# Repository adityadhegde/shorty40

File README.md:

# The Shorty40
An ortholinear 39key keyboard with a 2U spacebar and KMK support using a Raspberry Pi Pico

## Bill of Materials

### Cost Saving Open Build
* Printed circuit board
* Raspberry Pi Pico or clones with same dimensions and GPIO Layouts with male headers attached 
* 39 1N4148 Diodes - through hole version
* 39 CherryMX Compatible plate mount switches
* 38 1U Keycaps and 1 2U Keycaps
* 1 2U plate mount stabilizer
* 1 3D Printed key plate
* 1 Laser Cut bottom plate
* 4 M2 Stand-Offs with  minimum 20mm clearance
* 8 5mm M2 screws
* 4 adhesive silicone/rubber foot - recommended but not required

### Close Case Build
* Printed circuit board
* Raspberry Pi Pico or clones with same dimensions and GPIO Layouts 
* 2 20 Pin male headers for the Pi Pico
* 2 20 Pin male to female headers for PCB
* 39 1N4148 Diodes - through hole version
* Hot Swap Sockets - tested with Millmax 0305 Socket
* 39 CherryMX Compatible plate mount switches
* 38 1U Keycaps and 1 2U Keycaps
* 1 2U plate mount stabilizer
* 1 3D Printed key plate
* 1 3D Printed Case - testing in process
* 8 5mm M2 screws
* 4 adhesive silicone/rubber foot

## Software Setup
1. Install [circuit python](https://circuitpython.org/)
2. Get [KMK](https://github.com/KMKfw/kmk_firmware/archive/refs/heads/master.zip) and unzip the files on to the circuit-python/pi-pico drive
3. Replace the code.py and boot.py files on the Pi-Pico drive with the ones provided on this repository

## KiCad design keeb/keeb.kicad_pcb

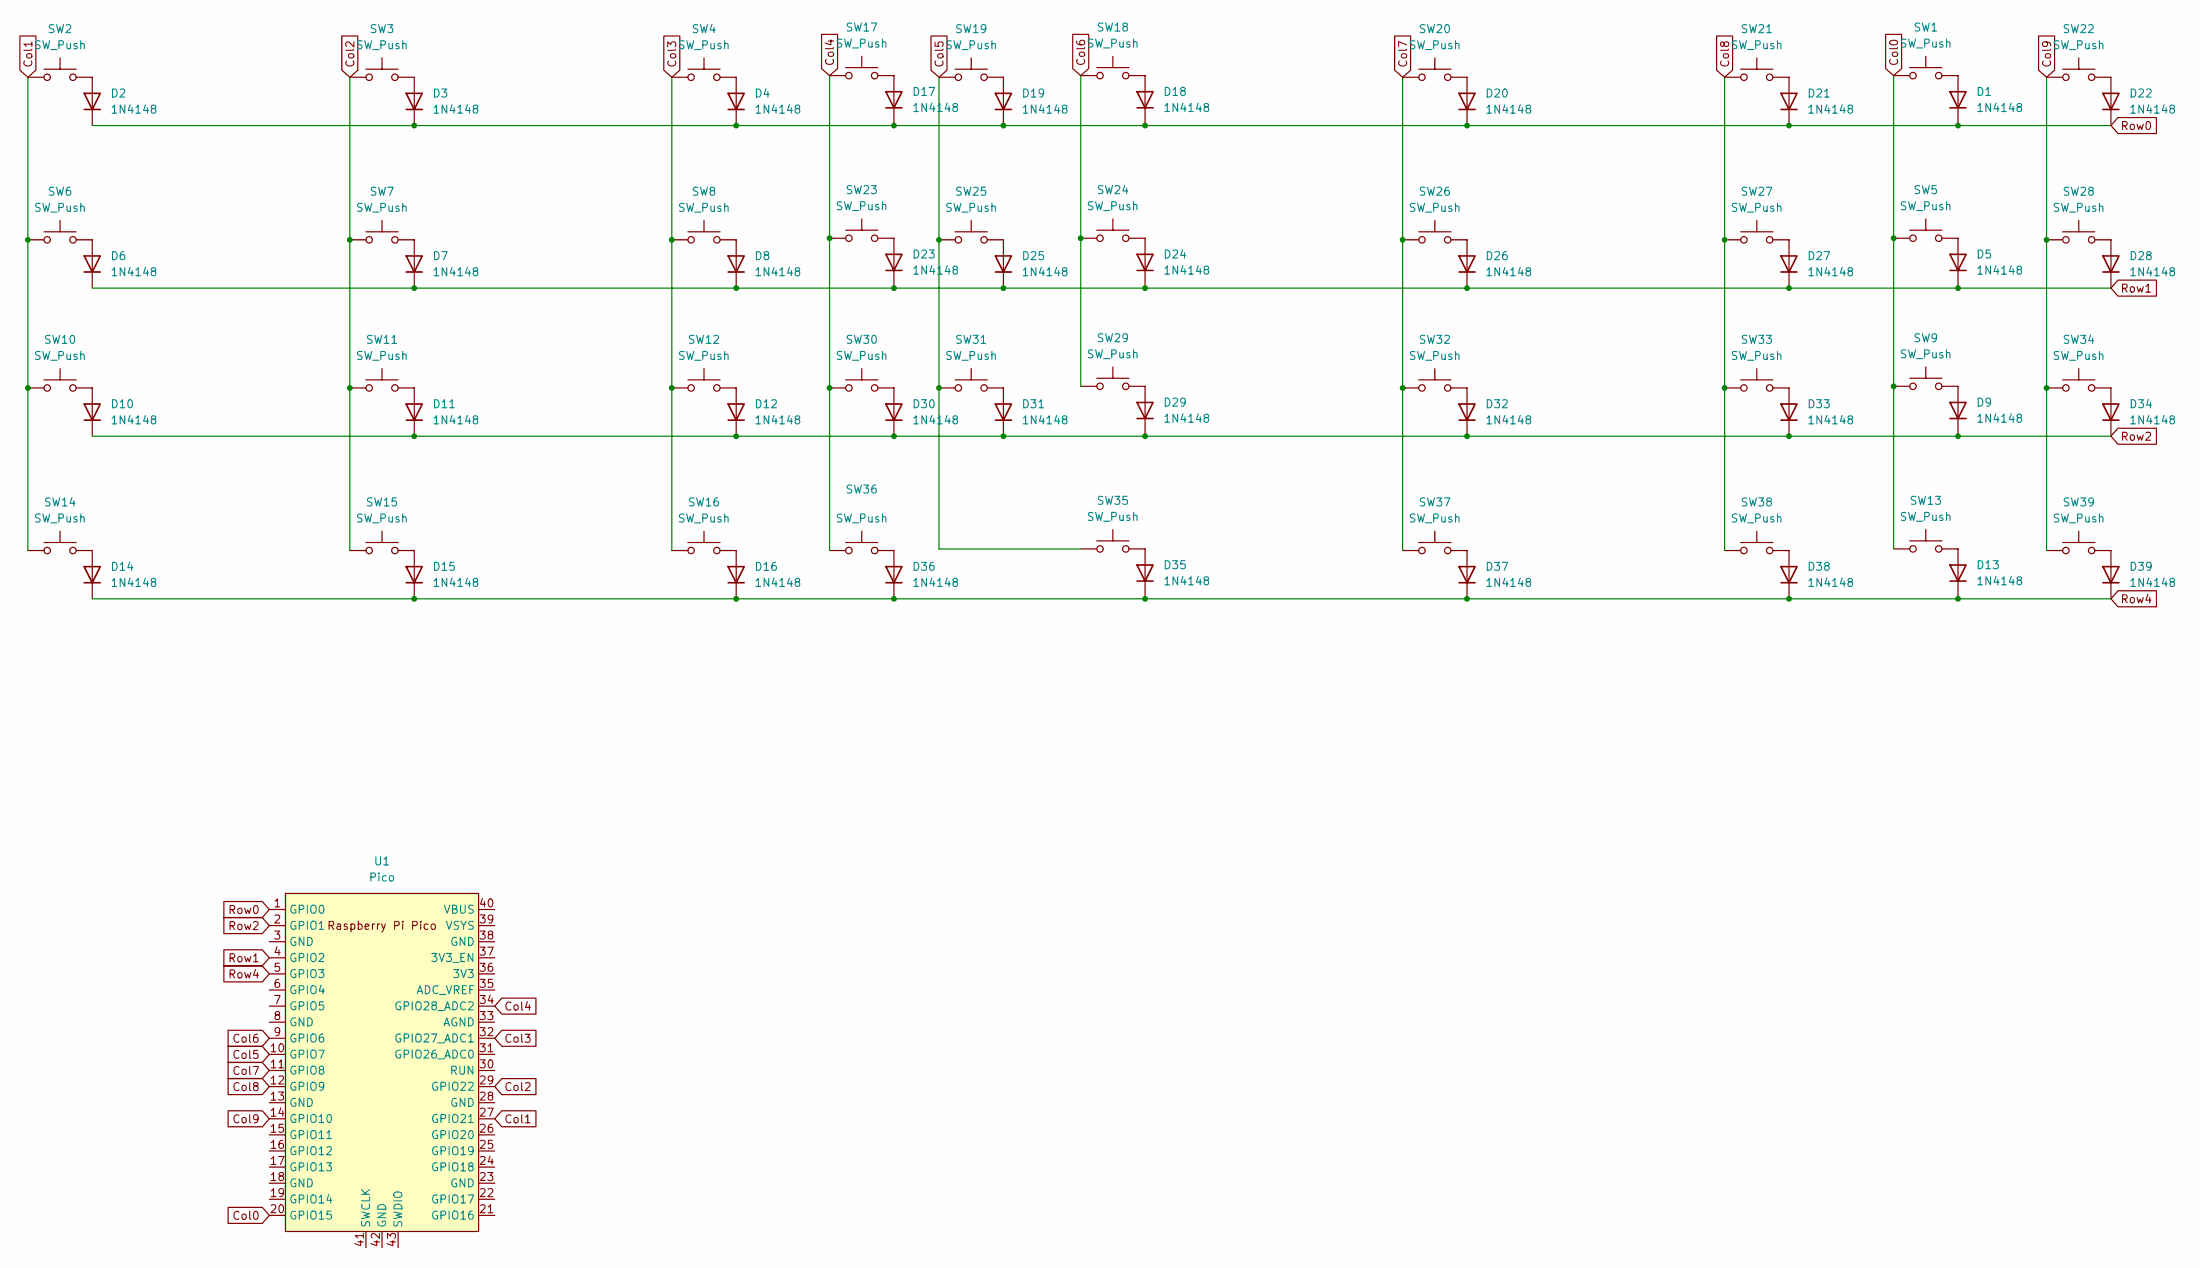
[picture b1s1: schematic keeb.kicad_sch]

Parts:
D1, D2, D3, D4, D5, D6, D7, D8, D9, D10, D11, D12, D13, D14, D15, D16, D17, D18, D19, D20, D21, D22, D23, D24, D25, D26, D27, D28, D29, D30, D31, D32, D33, D34, D35, D36, D37, D38, D39: 1N4148; Diotec_Semiconductor-1N4148-0
SW1, SW2, SW3, SW4, SW5, SW6, SW7, SW8, SW9, SW10, SW11, SW12, SW13, SW14, SW15, SW16, SW17, SW18, SW19, SW20, SW21, SW22, SW23, SW24, SW25, SW26, SW27, SW28, SW29, SW30, SW31, SW32, SW33, SW34, SW36, SW37, SW38, SW39: SW_Push; SW_Cherry_MX_1.00u_PCB
SW35: SW_Push; SW_Cherry_MX_2.00u_Plate
U1: Pico; RPi_Pico_SMD_TH

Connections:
Col0: SW1.1, SW5.1, SW9.1, SW13.1, U1.20 (GPIO15)
Col1: SW2.1, SW6.1, SW10.1, SW14.1, U1.27 (GPIO21)
Col2: SW3.1, SW7.1, SW11.1, SW15.1, U1.29 (GPIO22)
Col3: SW4.1, SW8.1, SW12.1, SW16.1, U1.32 (GPIO27_ADC1)
Col4: SW17.1, SW23.1, SW30.1, SW36.1, U1.34 (GPIO28_ADC2)
Col5: SW19.1, SW25.1, SW31.1, SW35.1, U1.10 (GPIO7)
Col6: SW18.1, SW24.1, SW29.1, U1.9 (GPIO6)
Col7: SW20.1, SW26.1, SW32.1, SW37.1, U1.11 (GPIO8)
Col8: SW21.1, SW27.1, SW33.1, SW38.1, U1.12 (GPIO9)
Col9: SW22.1, SW28.1, SW34.1, SW39.1, U1.14 (GPIO10)
unnamed: D1.2 (A), SW1.2
unnamed: D2.2 (A), SW2.2
unnamed: D3.2 (A), SW3.2
unnamed: D4.2 (A), SW4.2
unnamed: D5.2 (A), SW5.2
unnamed: D6.2 (A), SW6.2
unnamed: D7.2 (A), SW7.2
unnamed: D8.2 (A), SW8.2
unnamed: D9.2 (A), SW9.2
unnamed: D10.2 (A), SW10.2
unnamed: D11.2 (A), SW11.2
unnamed: D12.2 (A), SW12.2
unnamed: D13.2 (A), SW13.2
unnamed: D14.2 (A), SW14.2
unnamed: D15.2 (A), SW15.2
unnamed: D16.2 (A), SW16.2
unnamed: D17.2 (A), SW17.2
unnamed: D18.2 (A), SW18.2
unnamed: D19.2 (A), SW19.2
unnamed: D20.2 (A), SW20.2
unnamed: D21.2 (A), SW21.2
unnamed: D22.2 (A), SW22.2
unnamed: D23.2 (A), SW23.2
unnamed: D24.2 (A), SW24.2
unnamed: D25.2 (A), SW25.2
unnamed: D26.2 (A), SW26.2
unnamed: D27.2 (A), SW27.2
unnamed: D28.2 (A), SW28.2
unnamed: D29.2 (A), SW29.2
unnamed: D30.2 (A), SW30.2
unnamed: D31.2 (A), SW31.2
unnamed: D32.2 (A), SW32.2
unnamed: D33.2 (A), SW33.2
unnamed: D34.2 (A), SW34.2
unnamed: D35.2 (A), SW35.2
unnamed: D36.2 (A), SW36.2
unnamed: D37.2 (A), SW37.2
unnamed: D38.2 (A), SW38.2
unnamed: D39.2 (A), SW39.2
Row1: D5.1 (K), D6.1 (K), D7.1 (K), D8.1 (K), D23.1 (K), D24.1 (K), D25.1 (K), D26.1 (K), D27.1 (K), D28.1 (K), U1.4 (GPIO2)
Row2: D9.1 (K), D10.1 (K), D11.1 (K), D12.1 (K), D29.1 (K), D30.1 (K), D31.1 (K), D32.1 (K), D33.1 (K), D34.1 (K), U1.2 (GPIO1)

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
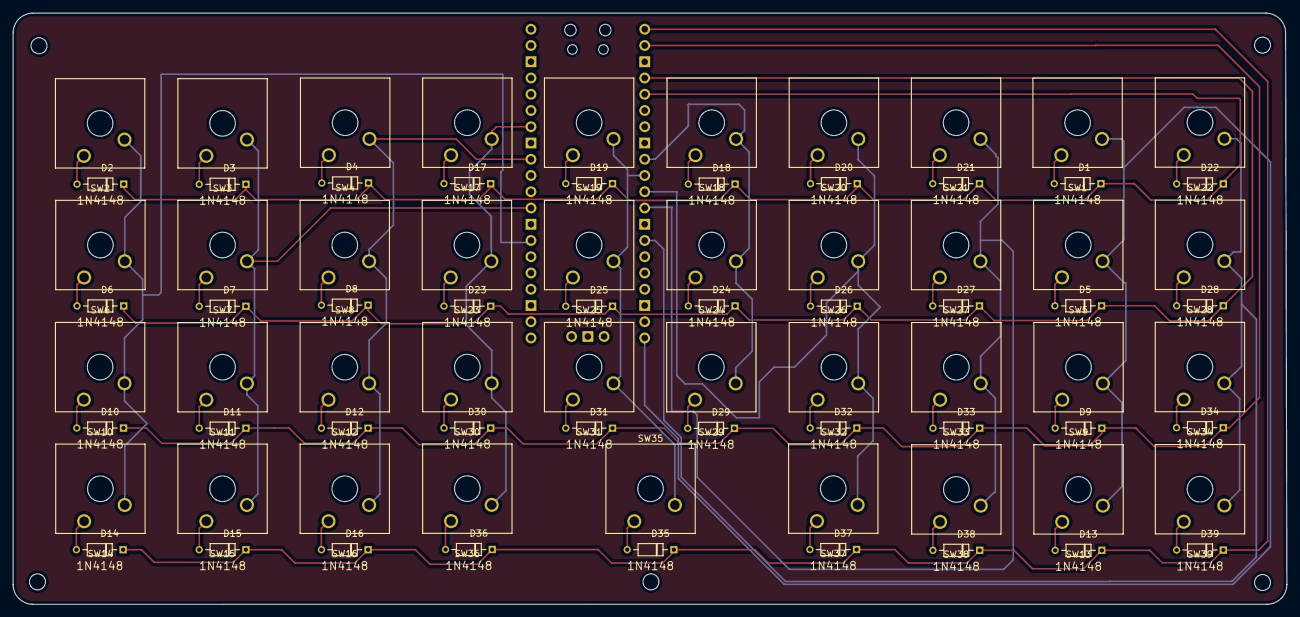
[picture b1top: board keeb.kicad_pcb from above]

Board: 2 copper layers, 199.1 x 92.4 mm, 79 parts (1 on the bottom side), 53 nets.

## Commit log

2023-05-14 BOM and corrections
2023-05-14 Software Setup Information
2023-05-21 case modifications, removed standoff near the pico and adjusted the USB port cut off
2023-05-21 updated keymap to add LALT key and box brackets
2023-05-21 MORE LAYOUT EFFICIENCY MODS
2023-05-31 fixed issues with boot file leading to fail while hiding storage
2023-05-31 string substitution support
